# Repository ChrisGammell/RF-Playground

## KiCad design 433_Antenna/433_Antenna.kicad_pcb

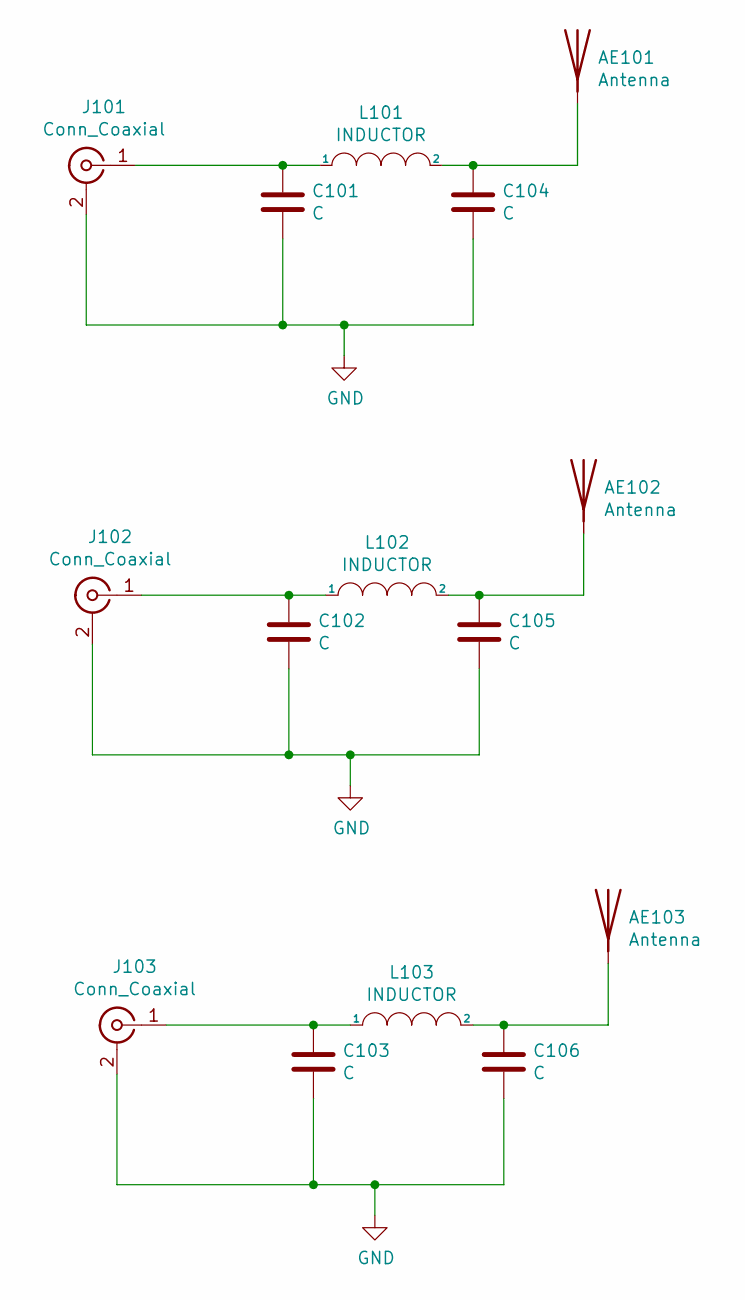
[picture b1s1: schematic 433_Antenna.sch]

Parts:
AE101: Antenna; 0p8x
AE102: Antenna; 1
AE103: Antenna; 1p2x
C101, C102, C103, C104, C105, C106: C; C_0402_1005Metric
J101, J102, J103: Conn_Coaxial; SMA_Amphenol_132134-11_Vertical
L101, L102, L103: INDUCTOR; C_0402_1005Metric

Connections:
GND: C101.2, C102.2, C103.2, C104.2, C105.2, C106.2, J101.2 (Ext), J102.2 (Ext), J103.2 (Ext)
unnamed: AE101.1, C104.1, L101.2
unnamed: AE102.1, C105.1, L102.2
unnamed: AE103.1, C106.1, L103.2
unnamed: C101.1, J101.1 (In), L101.1
unnamed: C102.1, J102.1 (In), L102.1
unnamed: C103.1, J103.1 (In), L103.1

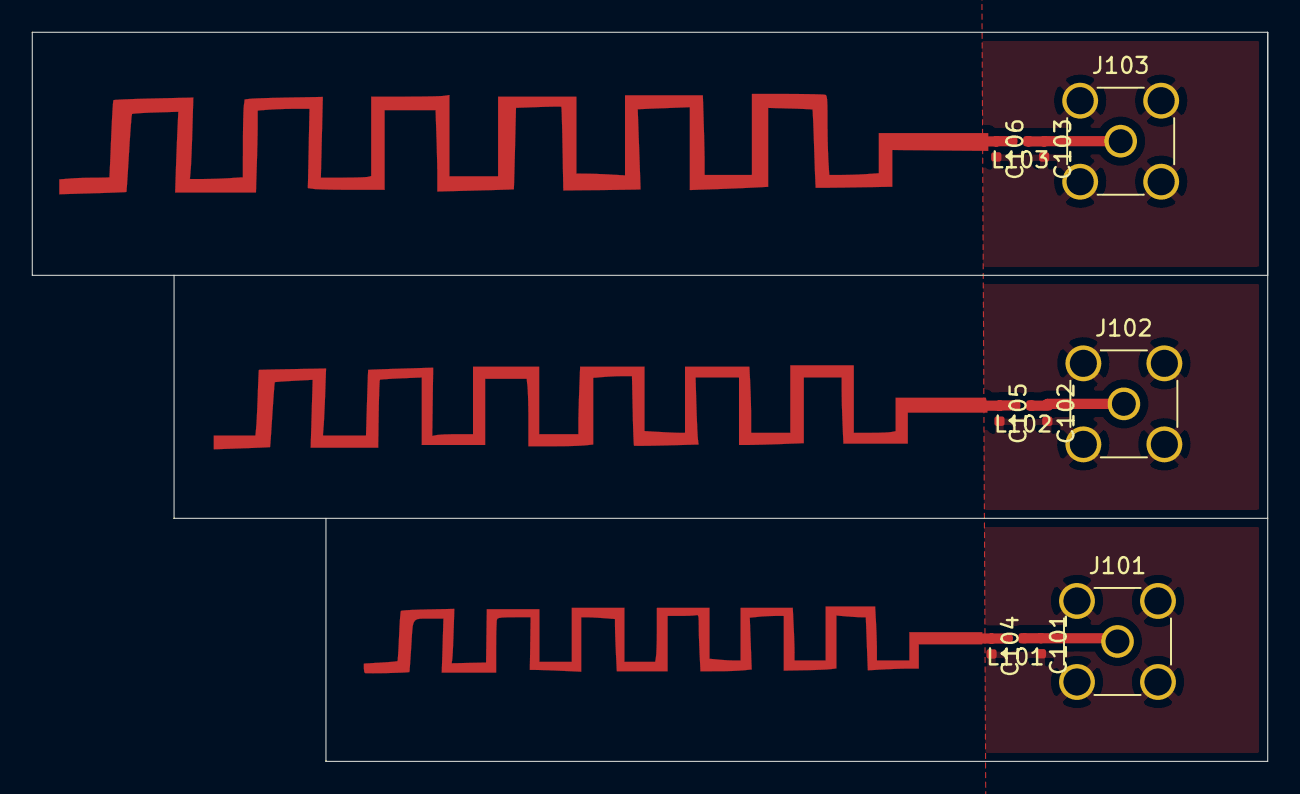
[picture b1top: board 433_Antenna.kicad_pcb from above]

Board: 2 copper layers, 77.5 x 45.7 mm, 15 parts (0 on the bottom side), 7 nets.

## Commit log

2019-10-21 Generated gerbers
2019-10-21 Small changes
